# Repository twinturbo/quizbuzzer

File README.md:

# quizbuzzer
https://docs.arduino.cc/built-in-examples/communication/MultiSerialMega

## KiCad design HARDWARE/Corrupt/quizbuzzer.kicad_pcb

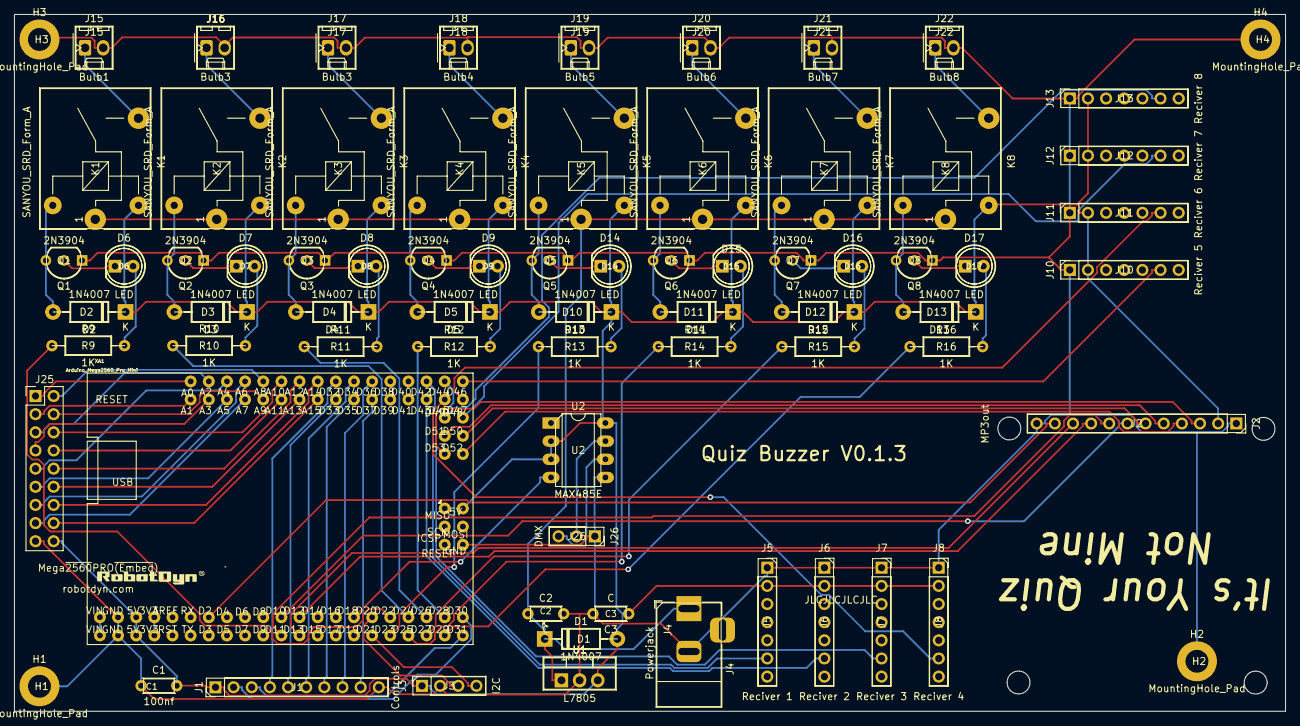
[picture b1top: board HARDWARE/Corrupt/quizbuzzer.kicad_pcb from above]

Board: 2 copper layers, 177.9 x 97.5 mm, 73 parts (0 on the bottom side), 89 nets.

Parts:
C1: 100nf; C_Disc_D4.3mm_W1.9mm_P5.00mm
C2, C3: C; C_Disc_D4.3mm_W1.9mm_P5.00mm
D1, D2, D3, D4, D5, D10, D11, D12, D13: 1N4007; D_DO-41_SOD81_P10.16mm_Horizontal
D6, D7, D8, D9, D14, D15, D16, D17: LED; LED_D5.0mm
H1, H2, H3, H4: MountingHole_Pad; MountingHole_3.2mm_M3_DIN965_Pad
J1: Controls; PinHeader_1x10_P2.54mm_Vertical
J2: MP3out; PinSocket_1x12_P2.54mm_Vertical
J3: I2C; PinSocket_1x04_P2.54mm_Vertical
J4: Powerjack; BarrelJack_Horizontal
J5: Reciver 1; PinSocket_1x07_P2.54mm_Vertical
J6: Reciver 2; PinSocket_1x07_P2.54mm_Vertical
J7: Reciver 3; PinSocket_1x07_P2.54mm_Vertical
J8: Reciver 4; PinSocket_1x07_P2.54mm_Vertical
J10: Reciver 5; PinSocket_1x07_P2.54mm_Vertical
J11: Reciver 6; PinSocket_1x07_P2.54mm_Vertical
J12: Reciver 7; PinSocket_1x07_P2.54mm_Vertical
J13: Reciver 8; PinSocket_1x07_P2.54mm_Vertical
J15: Bulb1; Molex_KK-254_AE-6410-02A_1x02_P2.54mm_Vertical
J16, J17: Bulb3; Molex_KK-254_AE-6410-02A_1x02_P2.54mm_Vertical
J18: Bulb4; Molex_KK-254_AE-6410-02A_1x02_P2.54mm_Vertical
J19: Bulb5; Molex_KK-254_AE-6410-02A_1x02_P2.54mm_Vertical
J20: Bulb6; Molex_KK-254_AE-6410-02A_1x02_P2.54mm_Vertical
J21: Bulb7; Molex_KK-254_AE-6410-02A_1x02_P2.54mm_Vertical
J22: Bulb8; Molex_KK-254_AE-6410-02A_1x02_P2.54mm_Vertical
J25: Conn_02x09_Odd_Even; PinHeader_2x09_P2.54mm_Vertical
J26: DMX; PinSocket_1x03_P2.54mm_Vertical
K1, K2, K3, K4, K5, K6, K7, K8: SANYOU_SRD_Form_A; Relay_SPST_SANYOU_SRD_Series_Form_A
Q1, Q2, Q3, Q4, Q5, Q6, Q7, Q8: 2N3904; TO-92_Inline_Wide
R9, R10, R11, R12, R13, R14, R15, R16: 1K; R_Axial_DIN0207_L6.3mm_D2.5mm_P10.16mm_Horizontal
U1: L7805; TO-220-3_Vertical
U2: MAX485E; DIP-8_W7.62mm_LongPads
XA1: Arduino_Mega2560_Pro_Mini; MEGA2560PRO-EMBED

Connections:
+5V: C1.2, C3.1, D1.2 (A), D2.1 (K), D3.1 (K), D4.1 (K), D5.1 (K), D10.1 (K), D11.1 (K), D12.1 (K), D13.1 (K), J1.1, J2.2, J3.1, J5.2, J6.2, J7.2, J8.2, J10.2, J11.2, J12.2, J13.2, J25.18, K1.2, K2.2, K3.2, K4.2, K5.2, K6.2, K7.2, K8.2, U1.3 (OUT), U2.2 (~RE), U2.3 (DE), U2.8 (VCC), XA1.5V1 (5V), XA1.5V2 (SPI_5V), XA1.5V3 (5V)
+12V: C2.1, D1.1 (K), J4.1, K1.1, K2.1, K3.1, K4.1, K5.1, K6.1, K7.1, K8.1, U1.1 (IN)
AUX-HEAD-1: J25.1, XA1.A0
AUX-HEAD-2: J25.3, XA1.A1
AUX-HEAD-3: J25.5, XA1.A2
AUX-HEAD-4: J25.7, XA1.A3
AUX-HEAD-5: J25.9, XA1.A4
AUX-HEAD-6: J25.11, XA1.A5
AUX-HEAD-7: J25.13, XA1.A6
AUX-HEAD-8: J25.15, XA1.A7
AUX-HEAD-9: J25.2, XA1.A8
AUX-HEAD-10: J25.4, XA1.A9
AUX-HEAD-11: J25.6, XA1.A10
AUX-HEAD-12: J25.8, XA1.A11
AUX-HEAD-13: J25.10, XA1.A12
AUX-HEAD-14: J25.12, XA1.A13
AUX-HEAD-15: J25.14, XA1.A14
AUX-HEAD-16: J25.16, XA1.A15
DMX-TX: U2.4 (DI), XA1.D18 (D18_TX1)
GND: C1.1, C2.2, C3.2, H1.1, H2.1, H3.1, H4.1, J1.10, J2.1, J2.12, J3.2, J4.2, J4.3, J5.1, J6.1, J7.1, J8.1, J10.1, J11.1, J12.1, J13.1, J15.2, J16.2, J17.2, J18.2, J19.2, J20.2, J21.2, J22.2, J25.17, J26.1, Q1.1 (E), Q2.1 (E), Q3.1 (E), Q4.1 (E), Q5.1 (E), Q6.1 (E), Q7.1 (E), Q8.1 (E), U1.2 (GND), U2.5 (GND), XA1.GND1 (GND), XA1.GND2 (GND), XA1.GND3 (GND)
Lamp1: R9.1, XA1.D22
Lamp2: R13.1, XA1.D23
Lamp3: R10.1, XA1.D24
Lamp4: R14.1, XA1.D25
Lamp5: R11.1, XA1.D26
Lamp6: R15.1, XA1.D27
Lamp7: R12.1, XA1.D28
Lamp8: R16.1, XA1.D29
MP3_EN: J2.11, XA1.D2 (D2_INT0)
unnamed: D2.2 (A), K1.5, Q1.3 (C)
unnamed: D3.2 (A), K2.5, Q2.3 (C)
unnamed: D4.2 (A), K3.5, Q3.3 (C)
unnamed: D5.2 (A), K4.5, Q4.3 (C)
unnamed: D6.2 (A), R9.2
unnamed: D6.1 (K), Q1.2 (B)
unnamed: D7.2 (A), R10.2
unnamed: D7.1 (K), Q2.2 (B)
unnamed: D8.2 (A), R11.2
unnamed: D8.1 (K), Q3.2 (B)
unnamed: D9.2 (A), R12.2
unnamed: D9.1 (K), Q4.2 (B)
unnamed: D10.2 (A), K5.5, Q5.3 (C)
unnamed: D11.2 (A), K6.5, Q6.3 (C)
unnamed: D12.2 (A), K7.5, Q7.3 (C)
unnamed: D13.2 (A), K8.5, Q8.3 (C)
unnamed: D14.2 (A), R13.2
unnamed: D14.1 (K), Q5.2 (B)
unnamed: D15.2 (A), R14.2
unnamed: D15.1 (K), Q6.2 (B)
unnamed: D16.2 (A), R15.2
unnamed: D16.1 (K), Q7.2 (B)
unnamed: D17.2 (A), R16.2
unnamed: D17.1 (K), Q8.2 (B)
unnamed: J1.2, XA1.D30
unnamed: J1.3, XA1.D31
unnamed: J1.4, XA1.D32
unnamed: J1.5, XA1.D33
unnamed: J1.6, XA1.D34
unnamed: J1.7, XA1.D35
unnamed: J1.8, XA1.D36
unnamed: J1.9, XA1.D37
unnamed: J15.1, K1.3
unnamed: J16.1, K2.3
unnamed: J17.1, K3.3
unnamed: J18.1, K4.3
unnamed: J19.1, K5.3
unnamed: J20.1, K6.3
unnamed: J21.1, K7.3
unnamed: J22.1, K8.3
unnamed: J26.2, U2.7 (B)
unnamed: J26.3, U2.6 (A)
PORTB_0: J2.3, XA1.D53 (D53_SS)
PORTB_1: J2.4, XA1.D52
PORTB_2: J2.5, XA1.D51
PORTB_3: J2.6, XA1.D50
PORTB_4: J2.7, XA1.D10
PORTB_5: J2.8, XA1.D11
PORTB_6: J2.9, XA1.D12
PORTB_7: J2.10, XA1.D13
Rec1: J5.6, XA1.D42
Rec2: J6.6, XA1.D43
Rec3: J7.6, XA1.D44
Rec4: J8.6, XA1.D45
Rec5: J10.6, XA1.D46
Rec6: J11.6, XA1.D47
Rec7: J12.6, XA1.D48
Rec8: J13.6, XA1.D49
SCL: J3.4, XA1.D21 (D21_SCL)
SDA: J3.3, XA1.D20 (D20_SDA)

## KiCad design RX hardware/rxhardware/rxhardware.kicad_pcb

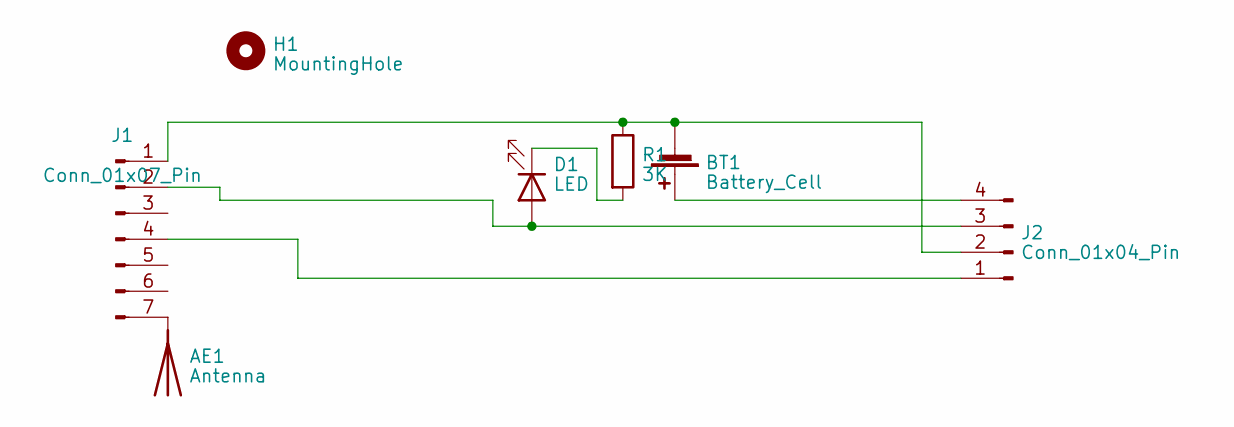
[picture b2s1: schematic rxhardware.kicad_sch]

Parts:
AE1: Antenna; PinHeader_1x01_P2.54mm_Vertical
BT1: Battery_Cell; CR2032-HOLDER-VERTICAL
D1: LED; LED_D3.0mm
H1: MountingHole; MountingHole_3.2mm_M3_DIN965_Pad
J1: Conn_01x07_Pin; PinHeader_1x07_P2.54mm_Vertical
J2: Conn_01x04_Pin; Molex_KK-254_AE-6410-04A_1x04_P2.54mm_Vertical
R1: 3K; R_Axial_DIN0204_L3.6mm_D1.6mm_P7.62mm_Horizontal

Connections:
unnamed: AE1.1 (A), J1.7
unnamed: BT1.1 (+), J2.4
unnamed: BT1.2 (-), J1.1, J2.2, R1.1
unnamed: D1.2 (A), J1.2, J2.3
unnamed: D1.1 (K), R1.2
unnamed: J1.4, J2.1

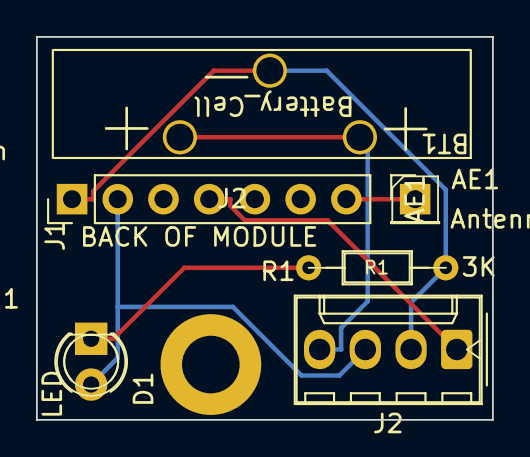
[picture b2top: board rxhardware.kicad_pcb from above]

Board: 2 copper layers, 25.3 x 21.3 mm, 7 parts (0 on the bottom side), 6 nets.

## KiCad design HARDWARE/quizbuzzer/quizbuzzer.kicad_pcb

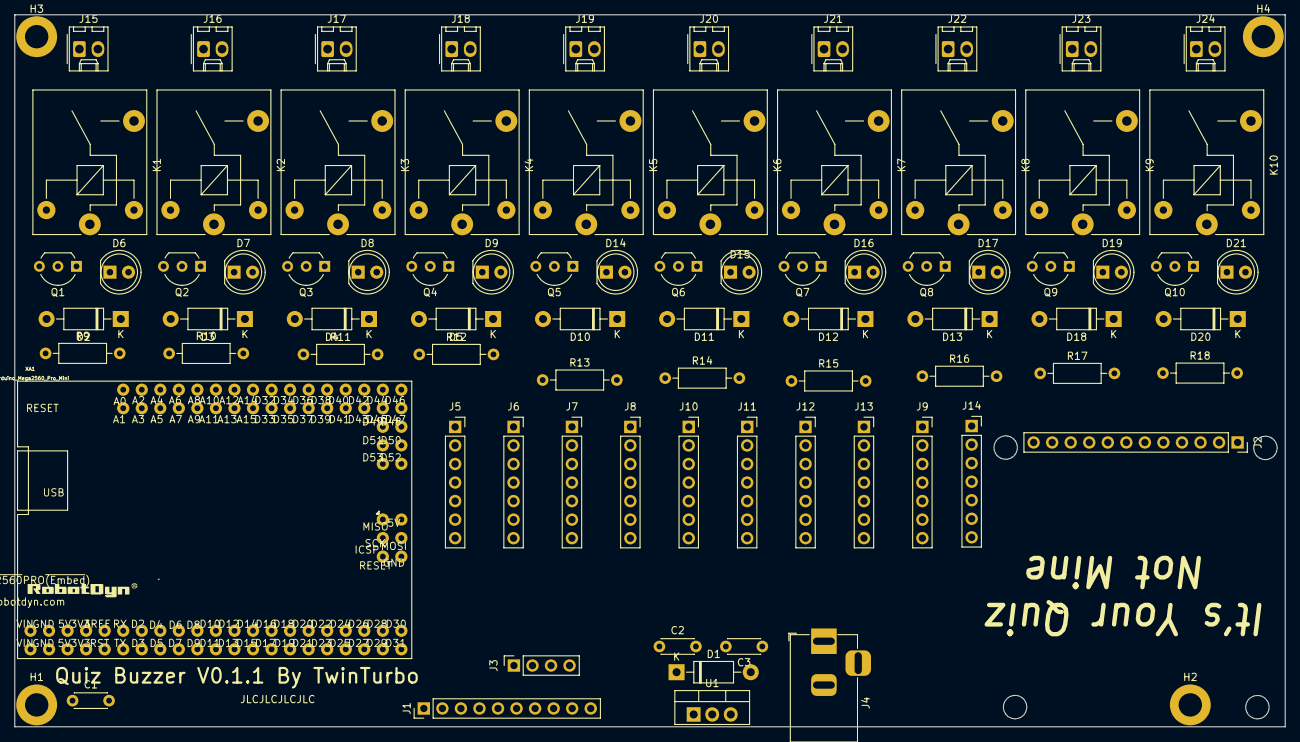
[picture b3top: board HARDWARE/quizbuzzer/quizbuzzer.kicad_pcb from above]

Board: 2 copper layers, 174.0 x 97.5 mm, 84 parts (0 on the bottom side), 82 nets, no tracks yet.

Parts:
C1: 100nf; C_Disc_D4.3mm_W1.9mm_P5.00mm
C2, C3: C; C_Disc_D4.3mm_W1.9mm_P5.00mm
D1, D2, D3, D4, D5, D10, D11, D12, D13, D18, D20: 1N4007; D_DO-41_SOD81_P10.16mm_Horizontal
D6, D7, D8, D9, D14, D15, D16, D17, D19, D21: LED; LED_D5.0mm
H1, H2, H3, H4: MountingHole_Pad; MountingHole_3.2mm_M3_DIN965_Pad
J1: Controls; PinHeader_1x10_P2.54mm_Vertical
J2: MP3out; PinSocket_1x12_P2.54mm_Vertical
J3: I2C; PinSocket_1x04_P2.54mm_Vertical
J4: Powerjack; BarrelJack_Horizontal
J5: Reciver 1; PinSocket_1x07_P2.54mm_Vertical
J6: Reciver 2; PinSocket_1x07_P2.54mm_Vertical
J7: Reciver 3; PinSocket_1x07_P2.54mm_Vertical
J8: Reciver 4; PinSocket_1x07_P2.54mm_Vertical
J9: Reciver 9; PinSocket_1x07_P2.54mm_Vertical
J10: Reciver 5; PinSocket_1x07_P2.54mm_Vertical
J11: Reciver 6; PinSocket_1x07_P2.54mm_Vertical
J12: Reciver 7; PinSocket_1x07_P2.54mm_Vertical
J13: Reciver 8; PinSocket_1x07_P2.54mm_Vertical
J14: Reciver 10; PinSocket_1x07_P2.54mm_Vertical
J15: Bulb1; Molex_KK-254_AE-6410-02A_1x02_P2.54mm_Vertical
J16, J17: Bulb3; Molex_KK-254_AE-6410-02A_1x02_P2.54mm_Vertical
J18: Bulb4; Molex_KK-254_AE-6410-02A_1x02_P2.54mm_Vertical
J19: Bulb5; Molex_KK-254_AE-6410-02A_1x02_P2.54mm_Vertical
J20: Bulb6; Molex_KK-254_AE-6410-02A_1x02_P2.54mm_Vertical
J21: Bulb7; Molex_KK-254_AE-6410-02A_1x02_P2.54mm_Vertical
J22: Bulb8; Molex_KK-254_AE-6410-02A_1x02_P2.54mm_Vertical
J23: Bulb9; Molex_KK-254_AE-6410-02A_1x02_P2.54mm_Vertical
J24: Bulb10; Molex_KK-254_AE-6410-02A_1x02_P2.54mm_Vertical
K1, K2, K3, K4, K5, K6, K7, K8, K9, K10: SANYOU_SRD_Form_A; Relay_SPST_SANYOU_SRD_Series_Form_A
Q1, Q2, Q3, Q4, Q5, Q6, Q7, Q8, Q9, Q10: 2N3904; TO-92_Inline_Wide
R9, R10, R11, R12, R13, R14, R15, R16, R17, R18: 1K; R_Axial_DIN0207_L6.3mm_D2.5mm_P10.16mm_Horizontal
U1: L7805; TO-220-3_Vertical
XA1: Arduino_Mega2560_Pro_Mini; MEGA2560PRO-EMBED

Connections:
+5V: C1.2, C3.1, D1.2, D2.1, D3.1, D4.1, D5.1, D10.1, D11.1, D12.1, D13.1, D18.1, D20.1, J1.1, J2.2, J3.4, J5.2, J6.2, J7.2, J8.2, J9.2, J10.2, J11.2, J12.2, J13.2, J14.2, K1.2, K2.2, K3.2, K4.2, K5.2, K6.2, K7.2, K8.2, K9.2, K10.2, U1.3, XA1.5V1, XA1.5V2, XA1.5V3
+12V: C2.1, D1.1, J4.1, K1.1, K2.1, K3.1, K4.1, K5.1, K6.1, K7.1, K8.1, K9.1, K10.1, U1.1
GND: C1.1, C2.2, C3.2, H1.1, H2.1, H3.1, H4.1, J1.10, J2.1, J2.12, J3.3, J4.2, J4.3, J5.1, J6.1, J7.1, J8.1, J9.1, J10.1, J11.1, J12.1, J13.1, J14.1, J15.2, J16.2, J17.2, J18.2, J19.2, J20.2, J21.2, J22.2, J23.2, J24.2, Q1.1, Q2.1, Q3.1, Q4.1, Q5.1, Q6.1, Q7.1, Q8.1, Q9.1, Q10.1, U1.2, XA1.GND1, XA1.GND2
Lamp1: R9.1, XA1.D13
Lamp2: R13.1, XA1.D22
Lamp3: R10.1, XA1.D23
Lamp4: R14.1, XA1.D24
Lamp5: R11.1, XA1.D25
Lamp6: R15.1, XA1.D26
Lamp7: R12.1, XA1.D27
Lamp8: R16.1, XA1.D28
Lamp9: R17.1, XA1.D29
Lamp10: R18.1, XA1.D30
unnamed: D2.2, K1.5, Q1.3
unnamed: D3.2, K2.5, Q2.3
unnamed: D4.2, K3.5, Q3.3
unnamed: D5.2, K4.5, Q4.3
unnamed: D6.1, Q1.2
unnamed: D6.2, R9.2
unnamed: D7.1, Q2.2
unnamed: D7.2, R10.2
unnamed: D8.1, Q3.2
unnamed: D8.2, R11.2
unnamed: D9.1, Q4.2
unnamed: D9.2, R12.2
unnamed: D10.2, K5.5, Q5.3
unnamed: D11.2, K6.5, Q6.3
unnamed: D12.2, K7.5, Q7.3
unnamed: D13.2, K8.5, Q8.3
unnamed: D14.1, Q5.2
unnamed: D14.2, R13.2
unnamed: D15.1, Q6.2
unnamed: D15.2, R14.2
unnamed: D16.1, Q7.2
unnamed: D16.2, R15.2
unnamed: D17.1, Q8.2
unnamed: D17.2, R16.2
unnamed: D18.2, K9.5, Q9.3
unnamed: D19.1, Q9.2
unnamed: D19.2, R17.2
unnamed: D20.2, K10.5, Q10.3
unnamed: D21.1, Q10.2
unnamed: D21.2, R18.2
unnamed: J1.2, XA1.D31
unnamed: J1.3, XA1.D32
unnamed: J1.4, XA1.D33
unnamed: J1.5, XA1.D34
unnamed: J1.6, XA1.D35
unnamed: J1.7, XA1.D36
unnamed: J1.8, XA1.D37
unnamed: J1.9, XA1.D38
unnamed: J2.3, XA1.D4
unnamed: J2.4, XA1.D5
unnamed: J2.5, XA1.D6
unnamed: J2.6, XA1.D7
unnamed: J2.7, XA1.D8
unnamed: J2.8, XA1.D9
unnamed: J2.9, XA1.D10
unnamed: J2.10, XA1.D11
unnamed: J2.11, XA1.D12
unnamed: J15.1, K1.3
unnamed: J16.1, K2.3
unnamed: J17.1, K3.3
unnamed: J18.1, K4.3
unnamed: J19.1, K5.3
unnamed: J20.1, K6.3
unnamed: J21.1, K7.3
unnamed: J22.1, K8.3
unnamed: J23.1, K9.3
unnamed: J24.1, K10.3
Rec1: J5.6, XA1.D44
Rec2: J6.6, XA1.D45
Rec3: J7.6, XA1.D46
Rec4: J8.6, XA1.D47
Rec5: J10.6, XA1.D48
Rec6: J11.6, XA1.D49
Rec7: J12.6, XA1.D50
Rec8: J13.6, XA1.D51
Rec9: J9.6, XA1.D52
Rec10: J14.6, XA1.D53
SCL: J3.1, XA1.D21
SDA: J3.2, XA1.D20

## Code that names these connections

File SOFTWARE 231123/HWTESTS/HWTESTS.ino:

//digital mp3//  IRELLIVENT CODE
int PORTB_1 = 4;
int PORTB_2 = 5;
int PORTB_3 = 6;
int PORTB_4 = 7;
int PORTB_5 = 50;
int PORTB_6 = 51;
int PORTB_7 = 52;
int PORTB_8 = 53;
int MP3_EN = 2;




void setup() {
  // put your setup code here, to run once:
  /*pinMode(11,OUTPUT);
  pinMode(PORTB_1, OUTPUT); digitalWrite(PORTB_1, LOW );
  pinMode(PORTB_2, OUTPUT); digitalWrite(PORTB_2, LOW );
  pinMode(PORTB_3, OUTPUT); digitalWrite(PORTB_3, LOW );
  pinMode(PORTB_4, OUTPUT); digitalWrite(PORTB_4, LOW );
  pinMode(PORTB_5, OUTPUT); digitalWrite(PORTB_5, LOW );
  pinMode(PORTB_6, OUTPUT); digitalWrite(PORTB_6, LOW );
  pinMode(PORTB_7, OUTPUT); digitalWrite(PORTB_7, LOW );
  pinMode(PORTB_8, OUTPUT); digitalWrite(PORTB_8, LOW );
  pinMode(MP3_EN, INPUT_PULLUP); */

  DDRB = B11111111;
}

void loop() {
  // put your main code here, to run repeatedly:
  /*digitalWrite(11,HIGH);
  delay(500);
  digitalWrite(11,LOW);
  delay(200);*/
  PORTB = B01111111;
  delay(2000); 
  PORTB = B10111111;
  delay(2000); 
  PORTB = B11011111;
  delay(2000); 
  PORTB = B11101111;
  delay(2000); 
  PORTB = B11101111;
  delay(2000); 
  PORTB = B11110111;
  delay(2000); 
  PORTB = B11111011;
  delay(2000); 
  PORTB = B11111101;
  delay(2000); 
  PORTB = B11111110;
  delay(2000); 
  PORTB = B11111111;
  delay(2000); 
}

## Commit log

2022-12-17 Initialised
2022-12-17 code state 1
2022-12-17 fix sound repetion in code
2022-12-21 schematic complete v0.1.0
2023-02-28 V0.1.0 sent to printer
2023-03-11 V0.1.1 Fixes
2023-04-04 DMX and AuxConnector
2023-04-08 move
2023-04-08 clean
2023-04-26 Updated schematic for portB, updated code with new variables, stuck at seetting pin mode in loop.
2023-04-28 10 way code cleanup in progress
2023-05-16 Code update
2023-05-16 commented out intergers..
    commented out team_bp integers.
2023-05-16 FIXLAYER
2023-05-16 corect
2023-05-25 holidaysync
2023-07-20 Sync Office
2023-11-01 SYNC
2023-11-03 Port Sort + 10 to 8 channel
2023-11-08 Code sanitisation part 1
2023-11-23 New Softwar After base working
2023-11-24 DMX SETUP WORKING
2023-11-25 DMX SAVE_LOAD
2023-11-26 DMX DATA VALIDATION
2023-11-29 Fixture Slecet + Move + 6 team
2023-11-29 Software New - 29
2023-12-01 Software fixes, tidy , OUT_OFF
2023-12-04 Mover Control, String Input, Audio Clip Management
2023-12-05 051223 Fixed, quoted string, need spectrapix and Drwoo
2023-12-16 RX re worked
2023-12-17 LCD added
2023-12-22 major updates
2023-12-24 Struct
2023-12-27 Tidy
2023-12-27 Tidy a
2023-12-28 BOOT OPTIONS, SCORE CONTROL, UTILITY MENU TO FINISH
2024-01-02 SPECTRAFIXED
2024-01-02 Menu Done, Quiz Battle, Minor Fixes
2024-01-03 QUIZBATTLE
2024-01-04 TS ARRAY
2024-01-04 Music , digital assignments of voices
2024-01-05 implementing slit string in sound output to reduce code side to one line per output type
2025-07-03 Fixing Corrupt
2025-07-03 Fixing Corrupt 2
